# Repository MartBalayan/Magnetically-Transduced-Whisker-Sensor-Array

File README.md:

# Magnetically Transduced Whisker Sensor Array

### Bio-Inspired Tactile Sensing | Embedded Systems | PCB Design | MuJoCo Simulation

A multidisciplinary engineering project involving the design and development of a bio-inspired whisker sensing system. The system uses magnetic transduction and Hall-effect sensors to detect mechanical interactions through changes in the relative position of magnets and sensors.

The project combines mechanical sensing, custom electronics, STM32 embedded firmware and MuJoCo simulation, resulting in both a functional hardware prototype and a simulation environment.

---

## 1. Project Overview

Whiskers are highly effective biological sensing structures that allow animals to perceive their surroundings through physical contact and mechanical feedback.

Inspired by this biological mechanism, this project investigates the development of an artificial whisker sensor array capable of detecting mechanical interactions using magnetic sensing technology.

The sensing principle relies on the relative displacement between a magnet and a Hall-effect sensor. When a whisker experiences mechanical deflection, the relative position of the magnet changes, producing a variation in the magnetic field measured by the sensor.

These variations are acquired and processed by an STM32 microcontroller, providing the electronic foundation for a tactile sensing system.

The project covers the development of both the physical sensing hardware and a MuJoCo simulation model for investigating whisker movement and mechanical interactions.

## 2. System Architecture

The system consists of three main engineering components:

### Magnetic Whisker Sensing

The sensing mechanism uses magnets and Hall-effect sensors to translate mechanical whisker displacement into measurable electrical signals.

The relative movement between the magnetic elements and sensors produces changes in the measured magnetic field, allowing mechanical interactions to be detected electronically.

### Embedded Processing — STM32

An STM32 microcontroller serves as the embedded processing platform.

The firmware provides the interface between the magnetic sensing hardware and the digital processing system.

### Mechanical Simulation — MuJoCo

A simulation environment developed using MuJoCo models whisker movement and mechanical interactions.

This provides a virtual environment for investigating the mechanical behavior of the whisker sensing structure.

## 3. Hardware Development

The physical prototype integrates the sensing elements, electronic circuitry and embedded processing hardware.

**Main hardware elements:**

- STM32 microcontroller
- Hall-effect magnetic sensors
- Permanent magnets
- Whisker sensing structures
- Custom-designed PCB
- Electronic interfacing and signal acquisition circuitry

The PCB design provides the electronic foundation for integrating the magnetic sensors with the embedded processing platform.

## 4. Embedded Firmware

The embedded software is developed for an STM32 microcontroller and is responsible for interfacing with the sensing electronics.

The firmware is organized within the STM32 project files included in this repository.

**Platform:** STM32

**Programming language:** Embedded C/C++

**Main focus:** Microcontroller-based sensor interfacing and data acquisition.

## 5. MuJoCo Simulation

The project includes a MuJoCo simulation environment developed to investigate the mechanical behavior of the whisker structures.

The simulation focuses on:

- Whisker movement and deflection.
- Mechanical interaction with surrounding objects.
- Behavior of the whisker structures under external interaction.
- Simulation-based investigation of the sensing mechanism.

The simulation complements the physical prototype by providing a virtual environment for studying the mechanical aspects of the sensing system.

## 6. Project Results

The development resulted in two complementary outcomes:

**Physical hardware prototype**
- Implementation of the magnetically transduced whisker sensing concept.
- Integration of Hall-effect sensors and magnetic elements.
- Custom PCB and STM32-based embedded electronics.

**Simulation environment**
- MuJoCo-based whisker model.
- Simulation of whisker movement.
- Investigation of mechanical interactions.

Together, these components demonstrate the implementation of a bio-inspired tactile sensing concept through both physical prototyping and simulation.

## 7. Repository Structure

```text
Magnetically-Transduced-Whisker-Sensor-Array/
│
├── Mujoco Simulation/
│   └── MuJoCo simulation files
│
├── PCB Design/
│   └── PCB design files
│
├── STM32 Core Files/
│   └── STM32 firmware and project files
│
├── A Magnetically Transdiced Whisker
│   Sensor Array - Masters Thesis.pdf
│
└── README.md
```

## 8. Technologies and Engineering Skills

| Category | Technology |
|---|---|
| Embedded Systems | STM32 |
| Programming | Embedded C/C++ |
| Magnetic Sensing | Hall-effect sensors |
| Electronics | PCB Design |
| Simulation | MuJoCo |
| Mechanical Systems | Whisker mechanics and deflection |
| System Development | Hardware-software integration |

## 9. Research Documentation

This project was developed as part of a Master's thesis.

The complete thesis contains the research background, engineering methodology, system development and detailed technical documentation.

[**Read the Master's Thesis (PDF)**](./A%20Magnetically%20Transdiced%20Whisker%20Sensor%20Array%20-%20Masters%20Thesis.pdf)

## 10. Project Information

| Attribute | Description |
|---|---|
| Project | Magnetically Transduced Whisker Sensor Array |
| Project Type | Master's Thesis / Engineering Research |
| Application Area | Bio-Inspired Tactile Sensing |
| Embedded Platform | STM32 |
| Magnetic Sensing | Hall-effect sensors |
| Simulation Environment | MuJoCo |
| Outcome | Working hardware prototype and simulation |

---

**Explore the implementation:** Browse the PCB design files, STM32 firmware and MuJoCo simulation included in this repository.

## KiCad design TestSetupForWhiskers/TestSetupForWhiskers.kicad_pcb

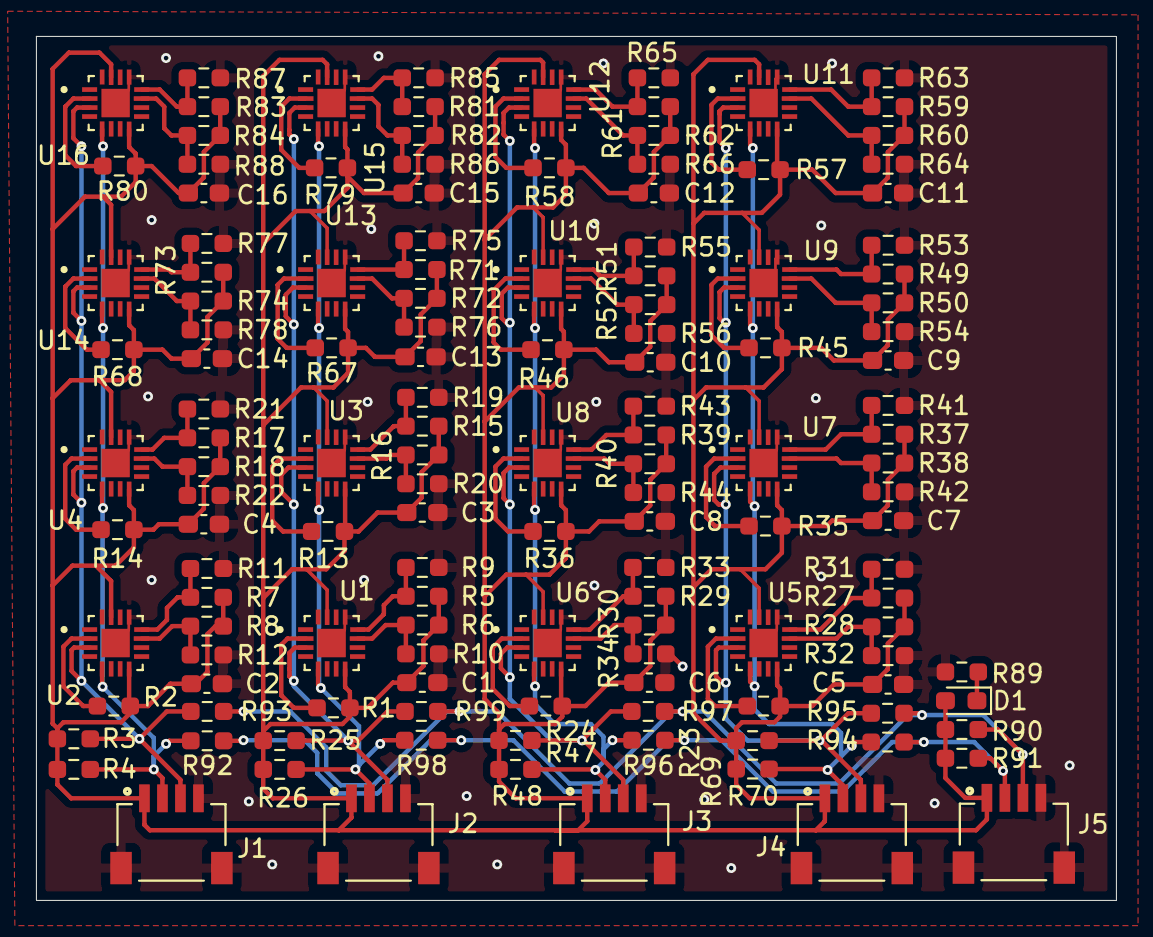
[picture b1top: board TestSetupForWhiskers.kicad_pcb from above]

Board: 2 copper layers, 60.0 x 48.0 mm, 137 parts (0 on the bottom side), 61 nets.

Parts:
C1, C2, C3, C4, C5, C6, C7, C8, C9, C10, C11, C12, C13, C14, C15, C16: 0.1u; C_0603_1608Metric_Pad1.08x0.95mm_HandSolder
D1: LED; LED_0603_1608Metric_Pad1.05x0.95mm_HandSolder
J1, J2, J3, J4, J5: SM04B-SRSS-TB_LF__SN_; JST_SM04B-SRSS-TB_LF__SN_
R1, R2, R3, R4, R9, R10, R11, R12, R13, R14, R19, R20, R21, R22, R23, R24, R25, R26, R31, R32, R33, R34, R35, R36, R41, R42, R43, R44, R45, R46, R47, R48, R53, R54, R55, R56, R57, R58, R63, R64, R65, R66, R67, R68, R69, R70, R75, R76, R77, R78, R79, R80, R85, R86, R87, R88, R90, R91: 10k; R_0603_1608Metric_Pad0.98x0.95mm_HandSolder
R5, R6, R7, R8, R15, R16, R17, R18, R27, R28, R29, R30, R37, R38, R39, R40, R49, R50, R51, R52, R59, R60, R61, R62, R71, R72, R73, R74, R81, R82, R83, R84, R92, R93, R94, R95, R96, R97, R98, R99: 0; R_0603_1608Metric_Pad0.98x0.95mm_HandSolder
R89: 2.2k; R_0603_1608Metric_Pad0.98x0.95mm_HandSolder
U1, U2, U3, U4: MLX90393ELW-ABA-011-SP; QFN50P300X300X100-17N
U5, U6, U7, U8: MLX90393ELW-ABA-012-SP; QFN50P300X300X100-17N
U9, U10, U11, U12: MLX90393ELW-ABA-013-SP; QFN50P300X300X100-17N
U13, U14, U15, U16: MLX90393ELW-ABA-014-SP; QFN50P300X300X100-17N

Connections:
3V3: C1.1, C2.1, C3.1, C4.1, C5.1, C6.1, C7.1, C8.1, C9.1, C10.1, C11.1, C12.1, C13.1, C14.1, C15.1, C16.1, D1.2 (A), J1.1, J2.1, J3.1, J4.1, J5.1, R1.2, R2.2, R3.1, R4.1, R5.2, R6.2, R7.2, R8.2, R13.2, R14.2, R15.2, R16.2, R17.2, R18.2, R23.2, R24.2, R25.1, R26.1, R27.2, R28.2, R29.2, R30.2, R35.2, R36.2, R37.2, R38.2, R39.2, R40.2, R45.2, R46.2, R47.1, R48.1, R49.2, R50.2, R51.2, R52.2, R57.2, R58.2, R59.2, R60.2, R61.2, R62.2, R67.2, R68.2, R69.1, R70.1, R71.2, R72.2, R73.2, R74.2, R79.2, R80.2, R81.2, R82.2, R83.2, R84.2, R90.1, R91.1, U1.8 (VDD_IO), U1.15 (VDD), U2.8 (VDD_IO), U2.15 (VDD), U3.8 (VDD_IO), U3.15 (VDD), U4.8 (VDD_IO), U4.15 (VDD), U5.8 (VDD_IO), U5.15 (VDD), U6.8 (VDD_IO), U6.15 (VDD), U7.8 (VDD_IO), U7.15 (VDD), U8.8 (VDD_IO), U8.15 (VDD), U9.8 (VDD_IO), U9.15 (VDD), U10.8 (VDD_IO), U10.15 (VDD), U11.8 (VDD_IO), U11.15 (VDD), U12.8 (VDD_IO), U12.15 (VDD), U13.8 (VDD_IO), U13.15 (VDD), U14.8 (VDD_IO), U14.15 (VDD), U15.8 (VDD_IO), U15.15 (VDD), U16.8 (VDD_IO), U16.15 (VDD)
A0_1: R5.1, R9.1, U1.12 (A0)
A0_2: R7.1, R11.1, U2.12 (A0)
A0_3: R15.1, R19.1, U3.12 (A0)
A0_4: R17.1, R21.1, U4.12 (A0)
A0_5: R27.1, R31.1, U5.12 (A0)
A0_6: R29.1, R33.1, U6.12 (A0)
A0_7: R37.1, R41.1, U7.12 (A0)
A0_8: R39.1, R43.1, U8.12 (A0)
A0_9: R49.1, R53.1, U9.12 (A0)
A0_10: R51.1, R55.1, U10.12 (A0)
A0_11: R59.1, R63.1, U11.12 (A0)
A0_12: R61.1, R65.1, U12.12 (A0)
A0_13: R71.1, R75.1, U13.12 (A0)
A0_14: R73.1, R77.1, U14.12 (A0)
A0_15: R81.1, R85.1, U15.12 (A0)
A0_16: R83.1, R87.1, U16.12 (A0)
A1_1: R6.1, R10.1, U1.11 (A1)
A1_2: R8.1, R12.1, U2.11 (A1)
A1_3: R16.1, R20.1, U3.11 (A1)
A1_4: R18.1, R22.1, U4.11 (A1)
A1_5: R28.1, R32.1, U5.11 (A1)
A1_6: R30.1, R34.1, U6.11 (A1)
A1_7: R38.1, R42.1, U7.11 (A1)
A1_8: R40.1, R44.1, U8.11 (A1)
A1_9: R50.1, R54.1, U9.11 (A1)
A1_10: R52.1, R56.1, U10.11 (A1)
A1_11: R60.1, R64.1, U11.11 (A1)
A1_12: R62.1, R66.1, U12.11 (A1)
A1_13: R72.1, R76.1, U13.11 (A1)
A1_14: R74.1, R78.1, U14.11 (A1)
A1_15: R82.1, R86.1, U15.11 (A1)
A1_16: R84.1, R88.1, U16.11 (A1)
GND: C1.2, C2.2, C3.2, C4.2, C5.2, C6.2, C7.2, C8.2, C9.2, C10.2, C11.2, C12.2, C13.2, C14.2, C15.2, C16.2, J1.4, J1.S1 (SHIELD), J1.S2 (SHIELD), J2.4, J2.S1 (SHIELD), J2.S2 (SHIELD), J3.4, J3.S1 (SHIELD), J3.S2 (SHIELD), J4.4, J4.S1 (SHIELD), J4.S2 (SHIELD), J5.4, J5.S1 (SHIELD), J5.S2 (SHIELD), R9.2, R10.2, R11.2, R12.2, R19.2, R20.2, R21.2, R22.2, R31.2, R32.2, R33.2, R34.2, R41.2, R42.2, R43.2, R44.2, R53.2, R54.2, R55.2, R56.2, R63.2, R64.2, R65.2, R66.2, R75.2, R76.2, R77.2, R78.2, R85.2, R86.2, R87.2, R88.2, R89.2, U1.13 (VSS), U1.17 (EXP), U2.13 (VSS), U2.17 (EXP), U3.13 (VSS), U3.17 (EXP), U4.13 (VSS), U4.17 (EXP), U5.13 (VSS), U5.17 (EXP), U6.13 (VSS), U6.17 (EXP), U7.13 (VSS), U7.17 (EXP), U8.13 (VSS), U8.17 (EXP), U9.13 (VSS), U9.17 (EXP), U10.13 (VSS), U10.17 (EXP), U11.13 (VSS), U11.17 (EXP), U12.13 (VSS), U12.17 (EXP), U13.13 (VSS), U13.17 (EXP), U14.13 (VSS), U14.17 (EXP), U15.13 (VSS), U15.17 (EXP), U16.13 (VSS), U16.17 (EXP)
unnamed: D1.1 (K), R89.1
unnamed: R1.1, U1.2 (MS/CS)
unnamed: R2.1, U2.2 (MS/CS)
unnamed: R13.1, U3.2 (MS/CS)
unnamed: R14.1, U4.2 (MS/CS)
unnamed: R23.1, U5.2 (MS/CS)
unnamed: R24.1, U6.2 (MS/CS)
unnamed: R35.1, U7.2 (MS/CS)
unnamed: R36.1, U8.2 (MS/CS)
unnamed: R45.1, U9.2 (MS/CS)
unnamed: R46.1, U10.2 (MS/CS)
unnamed: R57.1, U11.2 (MS/CS)
unnamed: R58.1, U12.2 (MS/CS)
unnamed: R67.1, U13.2 (MS/CS)
unnamed: R68.1, U14.2 (MS/CS)
unnamed: R79.1, U15.2 (MS/CS)
unnamed: R80.1, U16.2 (MS/CS)
SCL: J5.3, R90.2, R93.1, R95.1, R97.1, R99.1
SCL1: J1.3, R3.2, R93.2, U2.3 (SCL/SCLK), U4.3 (SCL/SCLK), U14.3 (SCL/SCLK), U16.3 (SCL/SCLK)
SCL2: J4.3, R69.2, R95.2, U5.3 (SCL/SCLK), U7.3 (SCL/SCLK), U9.3 (SCL/SCLK), U11.3 (SCL/SCLK)
SCL3: J3.3, R47.2, R97.2, U6.3 (SCL/SCLK), U8.3 (SCL/SCLK), U10.3 (SCL/SCLK), U12.3 (SCL/SCLK)
SCL4: J2.3, R25.2, R99.2, U1.3 (SCL/SCLK), U3.3 (SCL/SCLK), U13.3 (SCL/SCLK), U15.3 (SCL/SCLK)
SDA: J5.2, R91.2, R92.1, R94.1, R96.1, R98.1
SDA1: J1.2, R4.2, R92.2, U2.5 (SDA/MOSI), U4.5 (SDA/MOSI), U14.5 (SDA/MOSI), U16.5 (SDA/MOSI)
SDA2: J4.2, R70.2, R94.2, U5.5 (SDA/MOSI), U7.5 (SDA/MOSI), U9.5 (SDA/MOSI), U11.5 (SDA/MOSI)
SDA3: J3.2, R48.2, R96.2, U6.5 (SDA/MOSI), U8.5 (SDA/MOSI), U10.5 (SDA/MOSI), U12.5 (SDA/MOSI)
SDA4: J2.2, R26.2, R98.2, U1.5 (SDA/MOSI), U3.5 (SDA/MOSI), U13.5 (SDA/MOSI), U15.5 (SDA/MOSI)
